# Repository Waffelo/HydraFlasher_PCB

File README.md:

# HydraFlasher_PCB
Body for the Hydra.

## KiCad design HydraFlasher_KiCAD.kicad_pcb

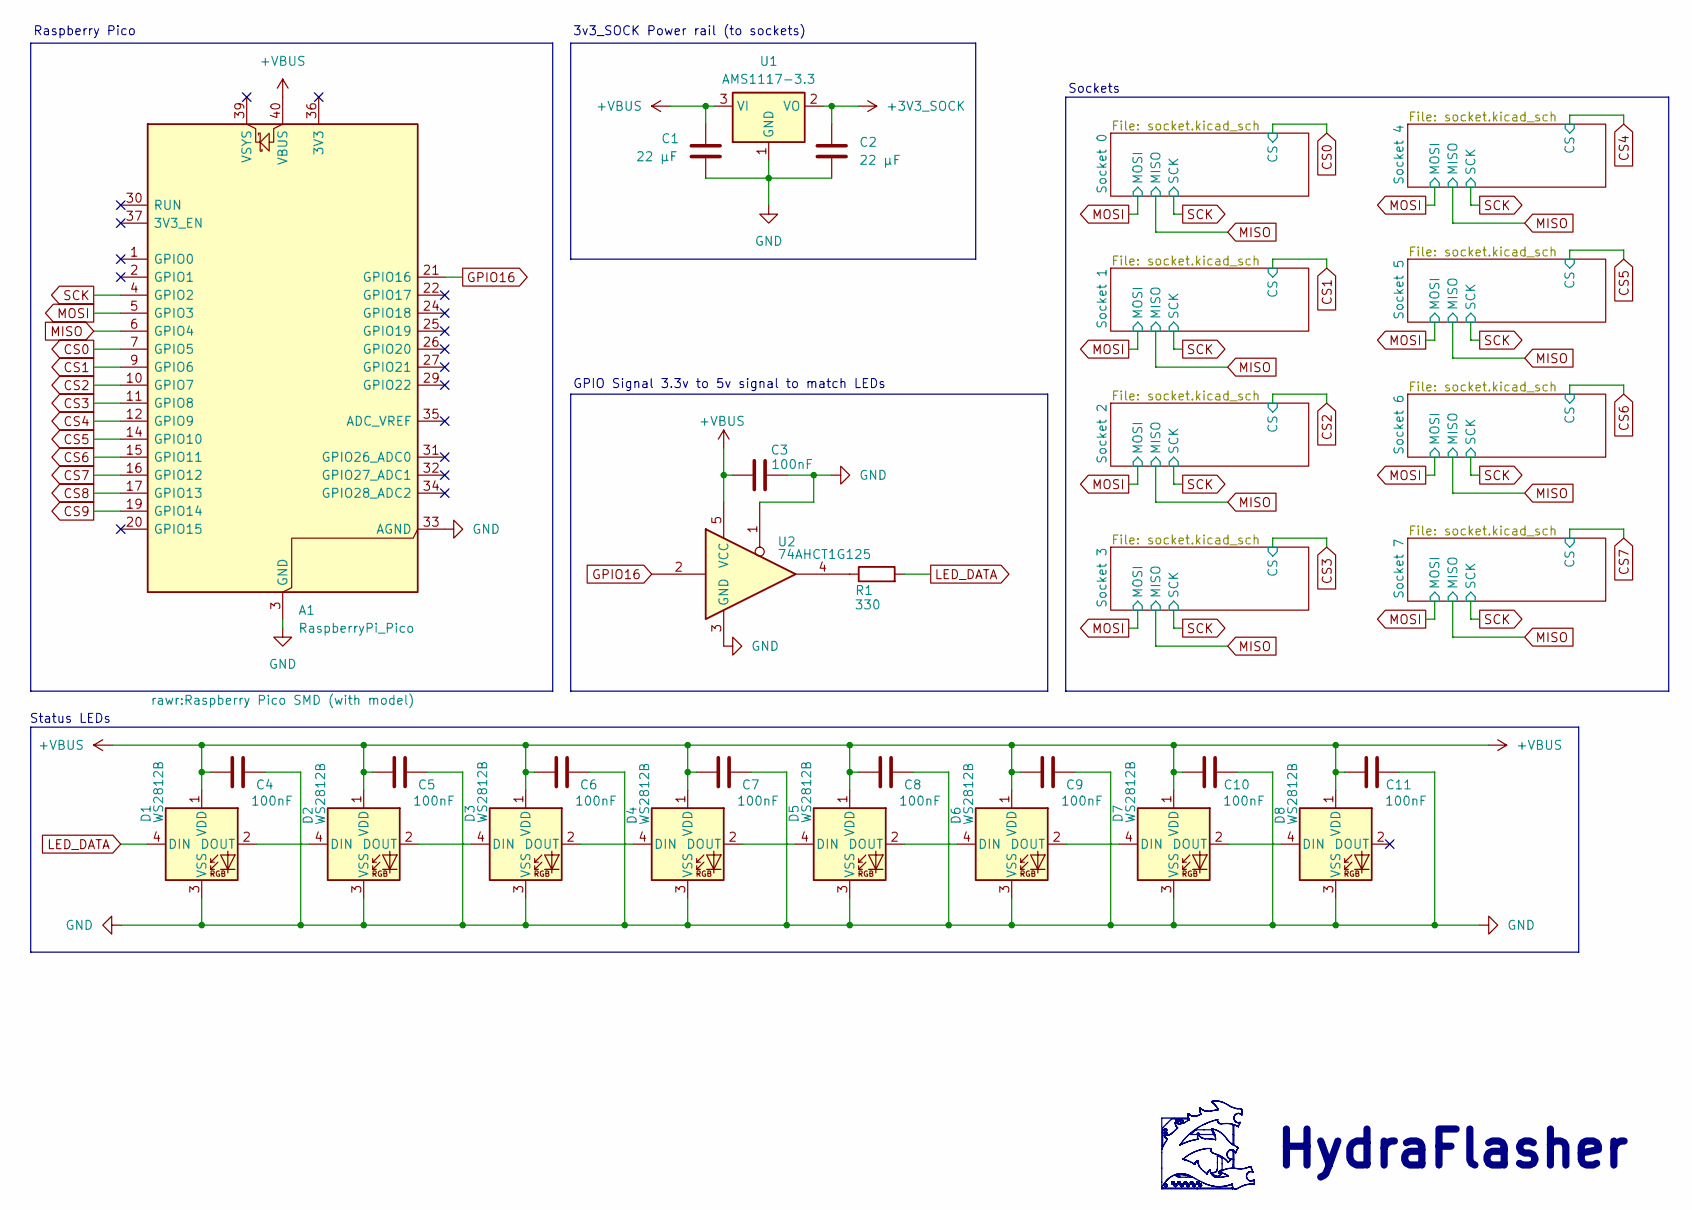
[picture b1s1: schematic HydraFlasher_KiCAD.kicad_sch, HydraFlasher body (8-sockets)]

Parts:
A1: RaspberryPi_Pico; Raspberry Pico SMD (with model); LCSC C7203002
C1, C2: 22 µF; C_0805_2012Metric_Pad1.18x1.45mm_HandSolder; MPN CC0805MKX5R8BB226; LCSC C784585
C3, C4, C5, C6, C7, C8, C9, C10, C11: 100nF; C_0805_2012Metric; LCSC C49678
D1, D2, D3, D4, D5, D6, D7, D8: WS2812B; LED_WS2812B_PLCC4_5.0x5.0mm_P3.2mm; LCSC C2843785
R1: 330; R_0805_2012Metric_Pad1.20x1.40mm_HandSolder; LCSC C17630
U1: AMS1117-3.3; SOT-223-3_TabPin2; MPN AMS1117-3.3; LCSC C6186
U2: 74AHCT1G125; SOT-23-5_HandSoldering; MPN SN74AHCT1G125DBVR; LCSC C7484

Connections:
+3V3_SOCK: C2.1, U1.2 (VO); also elsewhere on the board
+VBUS: A1.40 (VBUS), C1.1, C3.2, C4.1, C5.1, C6.1, C7.1, C8.1, C9.1, C10.1, C11.1, D1.1 (VDD), D2.1 (VDD), D3.1 (VDD), D4.1 (VDD), D5.1 (VDD), D6.1 (VDD), D7.1 (VDD), D8.1 (VDD), U1.3 (VI), U2.5 (VCC)
CS0: A1.7 (GPIO5); also elsewhere on the board
CS1: A1.9 (GPIO6); also elsewhere on the board
CS2: A1.10 (GPIO7); also elsewhere on the board
CS3: A1.11 (GPIO8); also elsewhere on the board
CS4: A1.12 (GPIO9); also elsewhere on the board
CS5: A1.14 (GPIO10); also elsewhere on the board
CS6: A1.15 (GPIO11); also elsewhere on the board
CS7: A1.16 (GPIO12); also elsewhere on the board
CS8: A1.17 (GPIO13)
CS9: A1.19 (GPIO14)
GND: A1.3 (GND), A1.8 (GND), A1.13 (GND), A1.18 (GND), A1.23 (GND), A1.28 (GND), A1.33 (AGND), A1.38 (GND), C1.2, C2.2, C3.1, C4.2, C5.2, C6.2, C7.2, C8.2, C9.2, C10.2, C11.2, D1.3 (VSS), D2.3 (VSS), D3.3 (VSS), D4.3 (VSS), D5.3 (VSS), D6.3 (VSS), D7.3 (VSS), D8.3 (VSS), U1.1 (GND), U2.1, U2.3 (GND); also elsewhere on the board
GPIO16: A1.21 (GPIO16), U2.2
LED_DATA: D1.4 (DIN), R1.2
MISO: A1.6 (GPIO4); also elsewhere on the board
MOSI: A1.5 (GPIO3); also elsewhere on the board
unnamed: D1.2 (DOUT), D2.4 (DIN)
unnamed: D2.2 (DOUT), D3.4 (DIN)
unnamed: D3.2 (DOUT), D4.4 (DIN)
unnamed: D4.2 (DOUT), D5.4 (DIN)
unnamed: D5.2 (DOUT), D6.4 (DIN)
unnamed: D6.2 (DOUT), D7.4 (DIN)
unnamed: D7.2 (DOUT), D8.4 (DIN)
unnamed: R1.1, U2.4
SCK: A1.4 (GPIO2); also elsewhere on the board

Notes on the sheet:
GPIO Signal 3.3v to 5v signal to match LEDs
Status LEDs
Sockets
HydraFlasher
3v3_SOCK Power rail (to sockets)
Raspberry Pico

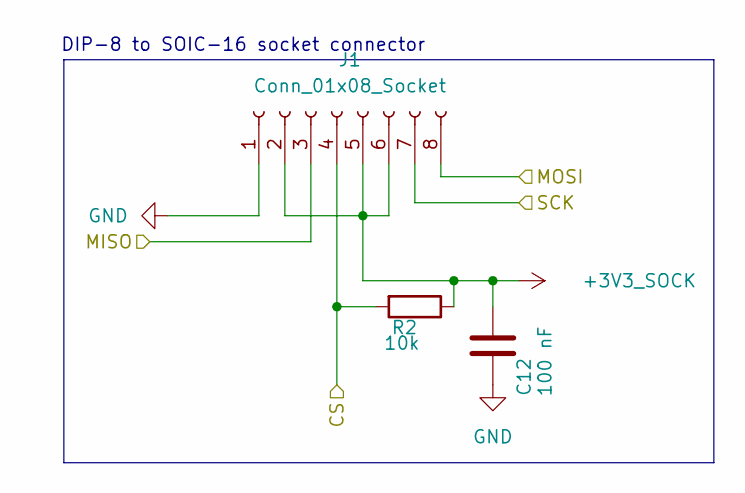
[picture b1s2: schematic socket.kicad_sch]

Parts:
C12: 100 nF; C_0603_1608Metric
J1: Conn_01x08_Socket; DIP8-Hydra
R2: 10k; R_0805_2012Metric_Pad1.20x1.40mm_HandSolder

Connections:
+3V3_SOCK: C12.2, J1.2, J1.5, J1.6, R2.1; also elsewhere on the board
CS0: J1.4, R2.2; also elsewhere on the board
GND: C12.1, J1.1; also elsewhere on the board
MISO: J1.3; also elsewhere on the board
MOSI: J1.8; also elsewhere on the board
SCK: J1.7; also elsewhere on the board

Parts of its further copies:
C13, C14, C15, C16, C17, C18, C19: 100 nF; C_0603_1608Metric
J2, J3, J4, J5, J6, J7, J8: Conn_01x08_Socket; DIP8-Hydra
R3, R4, R5, R6, R7, R8, R9: 10k; R_0805_2012Metric_Pad1.20x1.40mm_HandSolder

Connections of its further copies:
+3V3_SOCK: C13.2, C14.2, C15.2, C16.2, C17.2, C18.2, C19.2, J2.2, J2.5, J2.6, J3.2, J3.5, J3.6, J4.2, J4.5, J4.6, J5.2, J5.5, J5.6, J6.2, J6.5, J6.6, J7.2, J7.5, J7.6, J8.2, J8.5, J8.6, R3.1, R4.1, R5.1, R6.1, R7.1, R8.1, R9.1; also elsewhere on the board
CS1: J2.4, R3.2; also elsewhere on the board
CS2: J3.4, R4.2; also elsewhere on the board
CS3: J4.4, R5.2; also elsewhere on the board
CS4: J5.4, R6.2; also elsewhere on the board
CS5: J6.4, R7.2; also elsewhere on the board
CS6: J7.4, R8.2; also elsewhere on the board
CS7: J8.4, R9.2; also elsewhere on the board
GND: C13.1, C14.1, C15.1, C16.1, C17.1, C18.1, C19.1, J2.1, J3.1, J4.1, J5.1, J6.1, J7.1, J8.1; also elsewhere on the board
MISO: J2.3, J3.3, J4.3, J5.3, J6.3, J7.3, J8.3; also elsewhere on the board
MOSI: J2.8, J3.8, J4.8, J5.8, J6.8, J7.8, J8.8; also elsewhere on the board
SCK: J2.7, J3.7, J4.7, J5.7, J6.7, J7.7, J8.7; also elsewhere on the board

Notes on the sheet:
DIP-8 to SOIC-16 socket connector

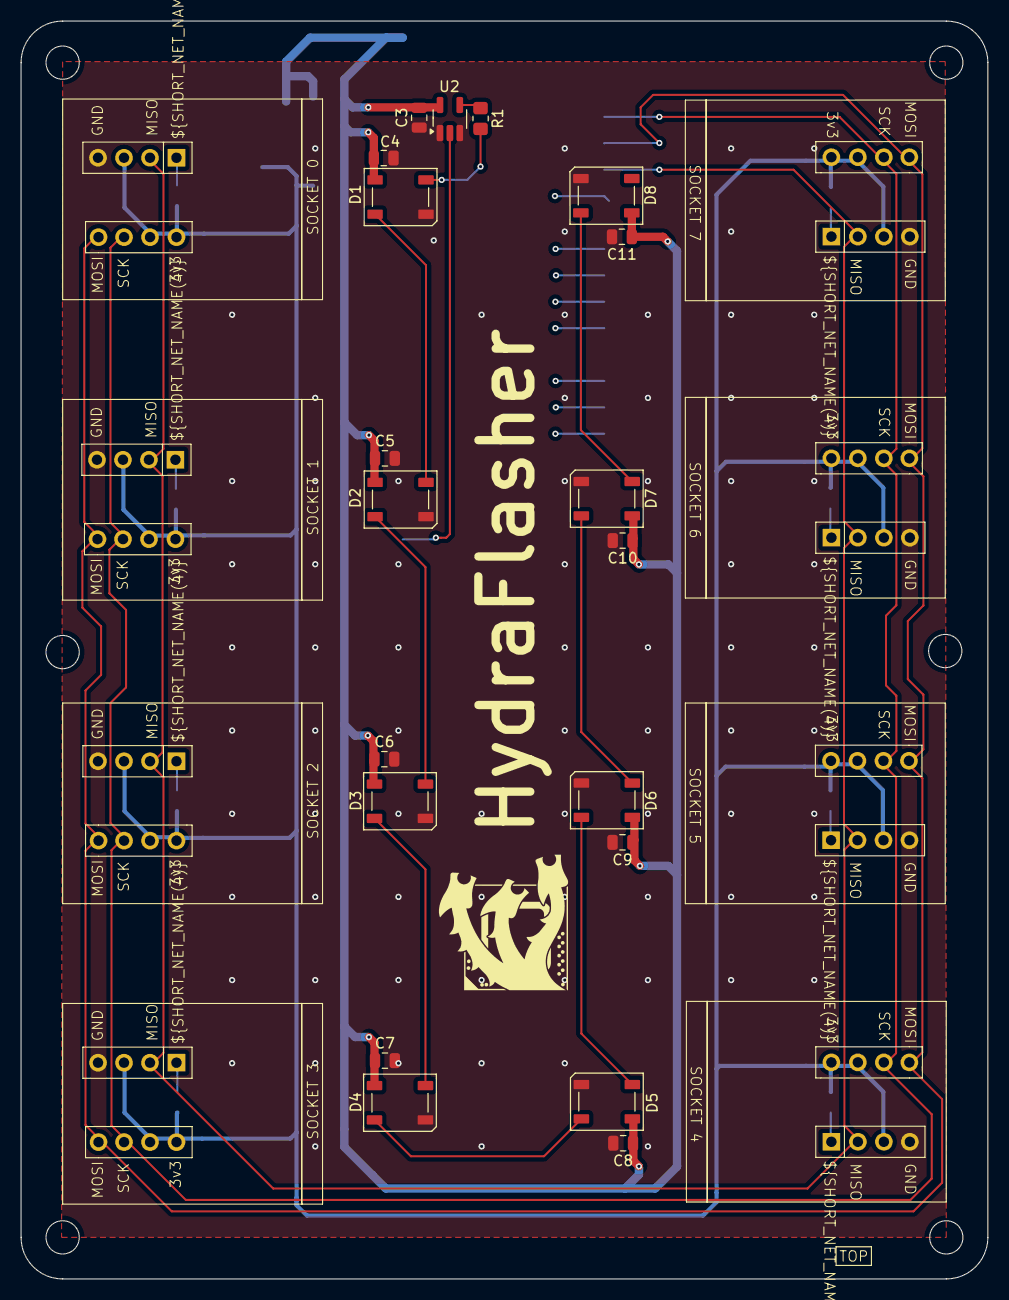
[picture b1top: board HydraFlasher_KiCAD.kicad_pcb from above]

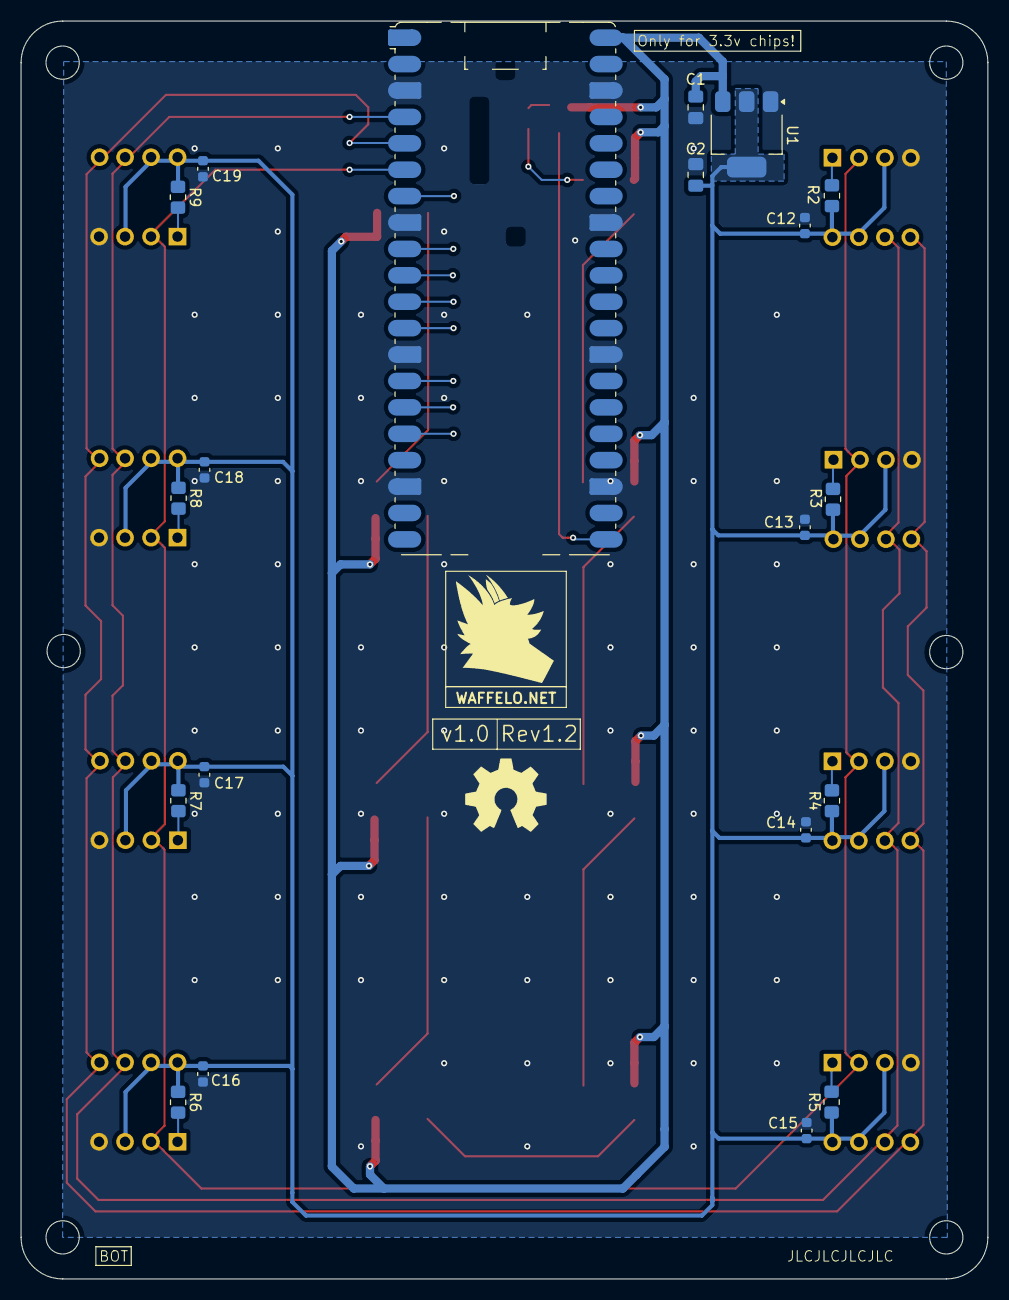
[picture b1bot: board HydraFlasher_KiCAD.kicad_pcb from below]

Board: 4 copper layers, 93.0 x 121.0 mm, 47 parts (20 on the bottom side), 24 nets.
